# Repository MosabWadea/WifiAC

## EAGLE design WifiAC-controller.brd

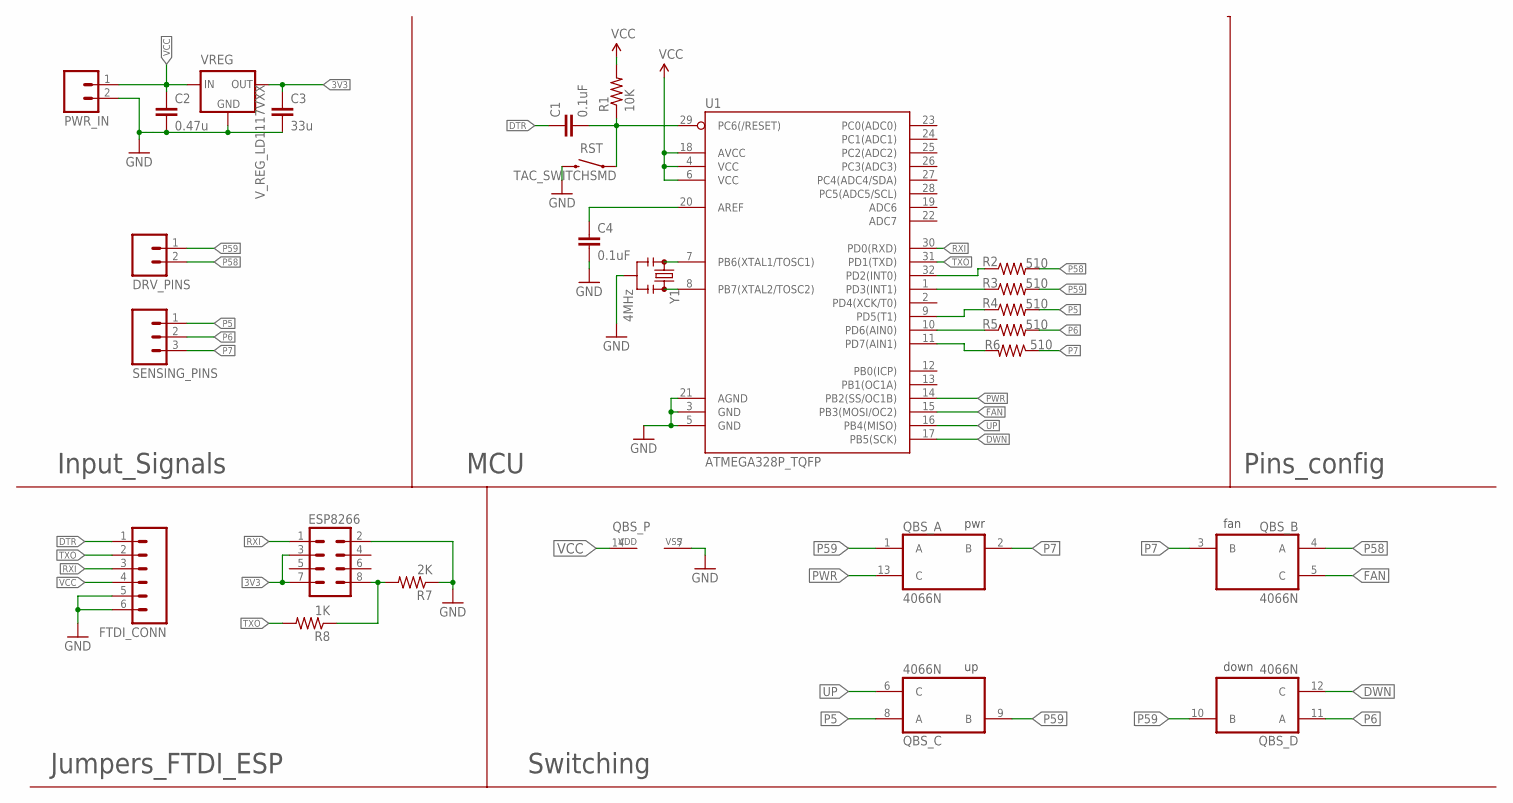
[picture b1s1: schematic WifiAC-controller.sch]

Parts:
C1, C4: 0.1uF; 0805
C2: 0.47u; 0805
C3: 33u; 0805
DRV_PINS: M02POLAR; MOLEX-1X2
ESP8266: M04X2; 2X4
FTDI_CONN: M06NO_SILK_FEMALE_PTH; 1X06_NO_SILK
PWR_IN: M02POLAR; MOLEX-1X2
QBS_: 4066N; DIL14
R1: 10K; 0805
R2, R3, R4, R5, R6: 510; 0805
R7: 2K; 0805
R8: 1K; 0805
RST: TAC_SWITCHSMD; TACTILE-SWITCH-SMD
SENSING_PINS: M03POLAR; MOLEX-1X3
U1: ATMEGA328P_TQFP; TQFP32-08
VREG: V_REG_LD1117VXX; 78XXL
Y1: 4MHz; RESONATOR-SMD_MED

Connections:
3V3: C3.1, ESP8266.3, ESP8266.7, VREG.GND (OUT)
DTR: C1.1, FTDI_CONN.1
DWN: QBS_.12 (C), U1.17 (PB5(SCK))
FAN: QBS_.5 (C), U1.15 (PB3(MOSI/OC2))
GND: C2.2, C3.2, C4.2, ESP8266.2, FTDI_CONN.5, FTDI_CONN.6, PWR_IN.2, QBS_.7 (VSS), R7.1, RST.3 (2), RST.4 (2), U1.3 (GND), U1.5 (GND), U1.21 (AGND), VREG.IN (GND), Y1.2
unnamed: C1.2, R1.1, RST.1, RST.2 (1), U1.29 (PC6(/RESET))
unnamed: C4.1, U1.20 (AREF)
unnamed: U1.7 (PB6(XTAL1/TOSC1)), Y1.1
unnamed: U1.8 (PB7(XTAL2/TOSC2)), Y1.3
unnamed: R2.1, U1.32 (PD2(INT0))
unnamed: R3.1, U1.1 (PD3(INT1))
unnamed: R4.1, U1.9 (PD5(T1))
unnamed: R5.1, U1.10 (PD6(AIN0))
unnamed: R6.2, U1.11 (PD7(AIN1))
unnamed: ESP8266.8, R7.2, R8.1
P5: QBS_.8 (A), R4.2, SENSING_PINS.1
P6: QBS_.11 (A), R5.2, SENSING_PINS.2
P7: QBS_.2 (B), QBS_.3 (B), R6.1, SENSING_PINS.3
P58: DRV_PINS.2, QBS_.4 (A), R2.2
P59: DRV_PINS.1, QBS_.1 (A), QBS_.9 (B), QBS_.10 (B), R3.2
PWR: QBS_.13 (C), U1.14 (PB2(SS/OC1B))
RXI: ESP8266.1, FTDI_CONN.3, U1.30 (PD0(RXD))
TXO: FTDI_CONN.2, R8.2, U1.31 (PD1(TXD))
UP: QBS_.6 (C), U1.16 (PB4(MISO))
VCC: C2.1, FTDI_CONN.4, PWR_IN.1, QBS_.14 (VDD), R1.2, U1.4 (VCC), U1.6 (VCC), U1.18 (AVCC), VREG.OUT (IN)

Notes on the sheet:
pwr
fan
down
Input_Signals
Switching
Pins_config
MCU
Jumpers_FTDI_ESP

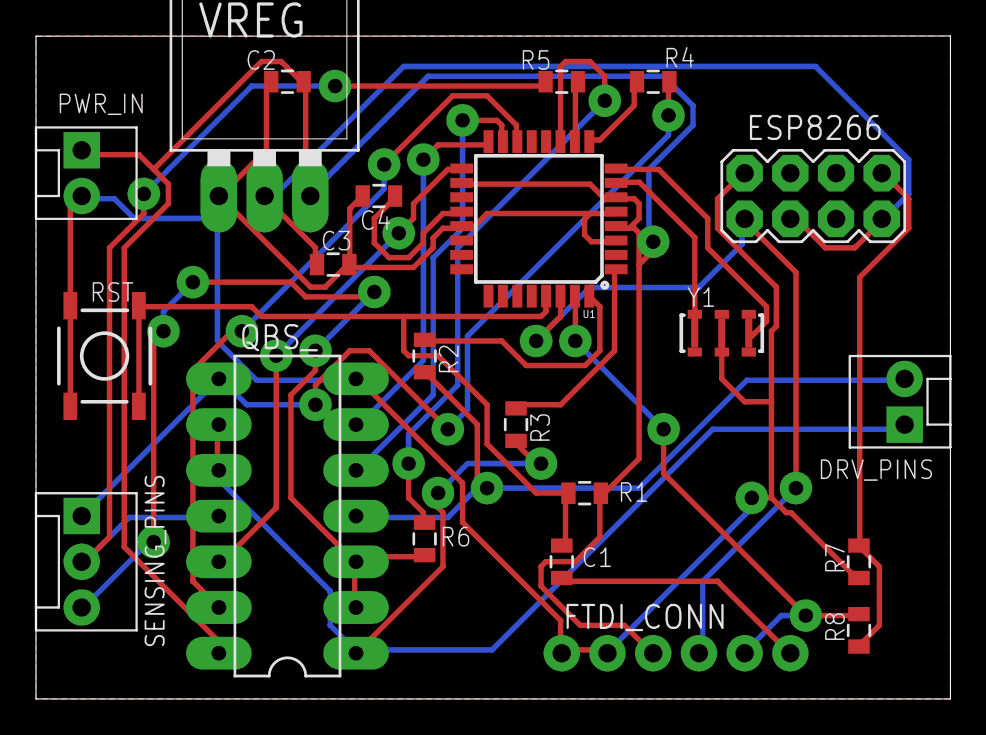
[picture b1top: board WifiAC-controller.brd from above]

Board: 2 copper layers, 50.8 x 36.8 mm, 23 parts (0 on the bottom side), 25 nets.

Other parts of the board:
_REFERENCE_HOLE_: _REFERENCE_HOLE_

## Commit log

2015-09-12 schematic created and esp lib added
2015-09-12 fixed schematic and generated layout
2015-09-12 minor fixes
2015-09-14 updated schematic to add input connections for the esp module
2015-09-14 updated layout
2015-09-14 fixes in layout and generated mill path and ref drills
2015-09-14 fixed GPIO connections and regenerated mill path with initial code added
2015-09-14 fixed gpio numbering, some more coding
2015-09-14 fixed code
2015-09-15 code finished for writing only without reading values
2015-10-04 major fixes, changed the esp foot print, changed the connections, changed power supply, made the layout smaller
2015-10-04 generated new mill path and cutting pref
2015-10-05 changed the smd capacitors to through hole
2015-10-05 fixed the pour millpath
2015-10-05 fixes in mill paths
2015-10-27 changing to generic esp but the circuit is not done
2015-10-27 updated the circuit and the output file. circuit update includes changing the esp package and adding an atmega328 as mcu
2015-10-27 reouted the pcb
2015-10-27 created output for pcb
2015-10-27 changed the wrong 0.2 clearance and rerouted the circuit
2015-10-27 generated and optimized mill path
2015-10-27 fixes in mill path and holes sizes
2015-11-05 mods
2015-11-23 generated the output for laster printing
2015-11-23 nothing changed
2015-12-01 added output file

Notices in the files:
parts and their libraries:
SparkFun-Connectors: Licensing: Creative Commons ShareAlike 4.0 International - https://creativecommons.org/licenses/by-sa/4.0
